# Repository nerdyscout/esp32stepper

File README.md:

# ESP32STEPPER

current state: untested :warning:

inspired by [joshr120/PD-Stepper](https://github.com/joshr120/PD-Stepper) but being fully open hardware/software.

Stepper motor controller using Trinamic TMC2208, ESP32-S3 and USB-PD mountable onto any NEMA17 motor. 

## Main Features:
- **ESP32-S3**
  - alternatively a LM555 pulse generator can be used.
- **USB Power Delivery** providing up to 20V operation
  - alternatively 9-24 Volt external supply 
- **TMC2208** silent stepper motor driver
- optional
  - rotary encoder:
    - **AS5048B** 14-Bit angular position sensor
    - **MPU-9250** 9-axis motion sensor
  - 0.96" 128x96 **LC-Display**
  - **BME280** temperature sensor
  - **QWIIC** connector for external I2C components
  - **JTAG** pins accessible
  - **3 GPIO** pins and **UART** available
  - 2x **WS2812** RGB LEDs
  - 2x **Push Buttons**

## PCB

### Schematic

### Bill of Materials

The complete BOM is available in different formats:
  - interactive [HTML](https://nerdyscout.github.io/esp32stepper/pcb/docs/bom/esp32stepper-ibom.html)
<!--  - [octopart](pcb/docs/bom/esp32stepper-octopart.csv) -->
  - [Excel](pcb/docs/bom/esp32stepper-bom.xlsx)

### Fabrication

#### Layout

<table border="0" width="100%">
  <tr>
    <th><strong>Top</strong></th>
    <th><strong>Bottom</strong></th>
  </tr>
  <tr>
    <td></td>
    <td></td>
  </tr>
</table>

All fabrication files needed to produce this PCB are located within the [release package](https://github.com/nerdyscout/esp32stepper/releases).

#### Assembly Variants

There are two options to power this board, do not connect both at the same time!
- via connector *PWR* an **external 9-24 Voltage** can be applied which than also will be used to power the stepper motor. 
- **USB-PD** by setting the CFG pins a voltage is selected. This can be made either by assembling the resistors or in firmware of the ESP32.

There are as well two options for controlling the board:
- The **LM555** gives some basic PWM frequency driving the stepper controller. Instead of the external rotary encoder a potentiometer can be connected and choosing R15, R16 and C18 correctly should allow any stepping frequency.
- using the **ESP32-S3** gives much more options as it allows to utilize the I2C components (LC Display, accelerometer, temperature sensor), two RGB Leds and dynamically sets USB voltage.

Microstepping can be enabled by setting jumper MS1 and MS2.

## Mechanics

in the folder `cad` the spacers between motor and PCB, as well as the top housing, can be found. The spacer below the stepper controller should be made out of metal so it could act as heat sink, the other part can be simply 3D printed. If the external power connector is not assembled those two spacer parts could be manufactured with less hight, this brings the hall sensor closer to the magnet which needs to be glued onto the motor axis. 

## Firmware

### ESPHome

There is a [esphome](https://esphome.io/) config file supporting various features located at `firmware/esphome`

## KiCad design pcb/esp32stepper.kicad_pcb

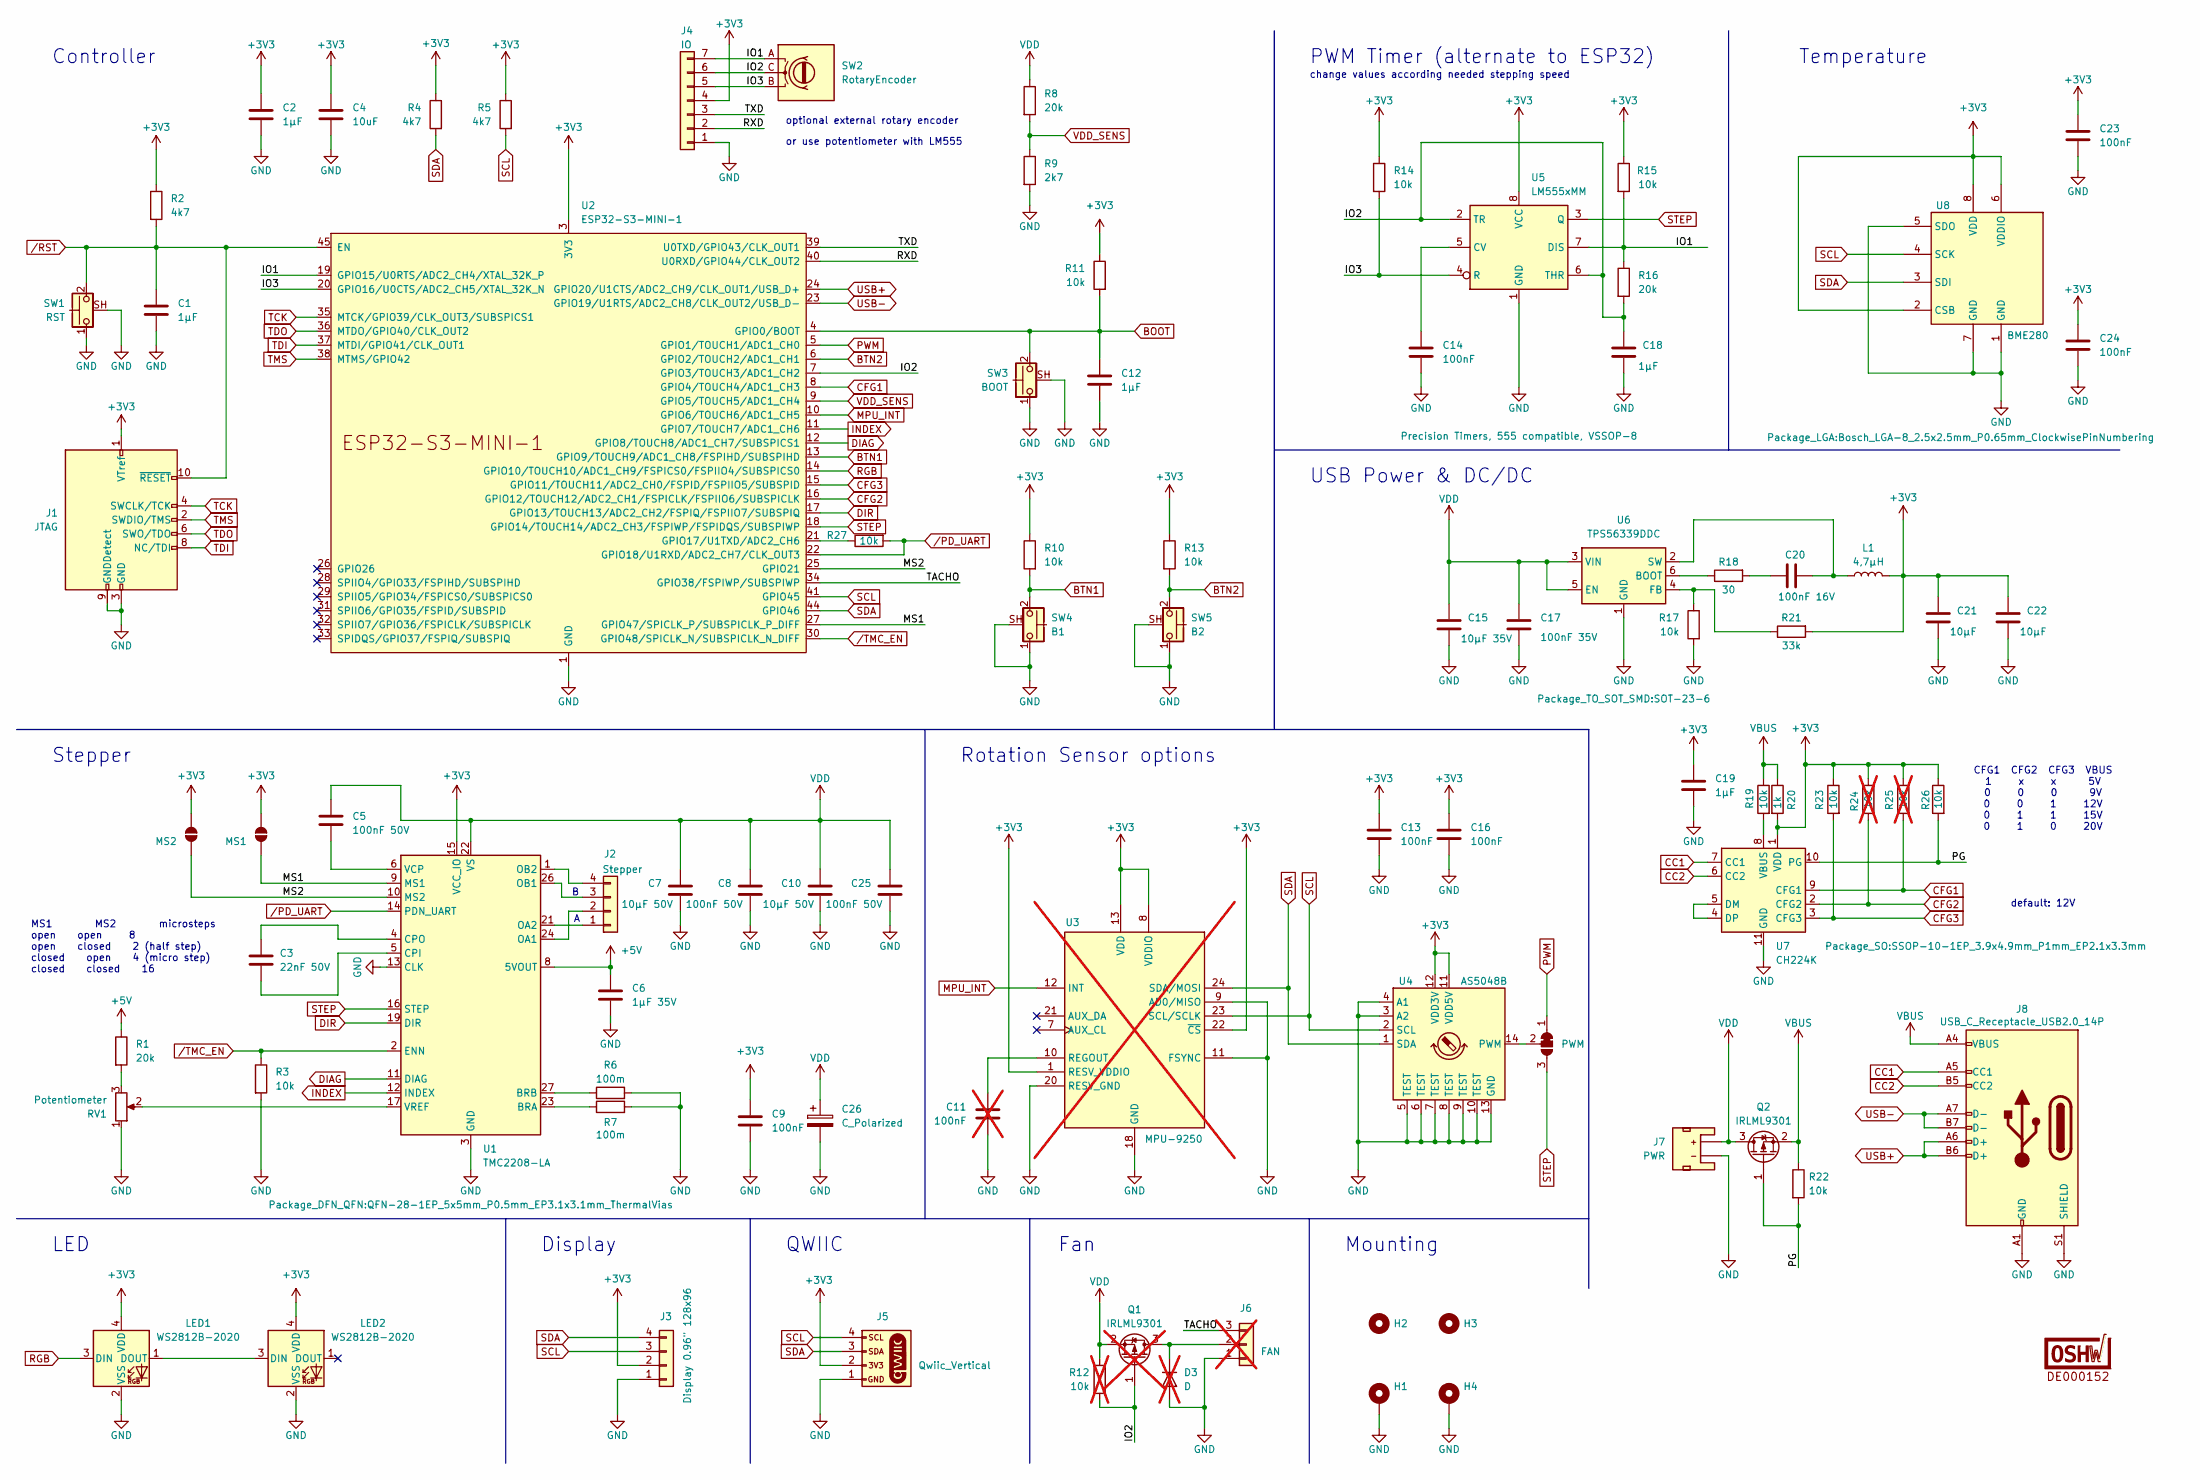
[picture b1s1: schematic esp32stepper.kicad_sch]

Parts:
C1, C2, C12, C19: 1µF; C_0402_1005Metric; LCSC C14445
C3: 22nF 50V; C_0402_1005Metric; LCSC C380305
C4: 10uF; C_0603_1608Metric; LCSC C22367827
C5, C8, C25: 100nF 50V; C_0603_1608Metric; LCSC C91183
C6: 1µF 35V; C_0603_1608Metric; LCSC C7432774
C7, C10: 10µF 50V; C_1206_3216Metric; LCSC C7432781
C9, C13, C16, C23, C24: 100nF; C_0402_1005Metric; LCSC C7432762
C11: 100nF; C_0402_1005Metric_Pad0.74x0.62mm_HandSolder; LCSC C7432762; not fitted
C14: 100nF; C_0402_1005Metric_Pad0.74x0.62mm_HandSolder; LCSC C7432762
C15: 10µF 35V; C_0603_1608Metric; LCSC C22367827
C17: 100nF 35V; C_0603_1608Metric; LCSC C5342943
C18: 1µF; C_0603_1608Metric_Pad1.08x0.95mm_HandSolder
C20: 100nF 16V; C_0402_1005Metric; LCSC C7432762
C21, C22: 10µF; C_0402_1005Metric; LCSC C5252392
C26: C_Polarized; CP_Elec_5x5.4; LCSC C22387982
D3: D; D_SOD-123; LCSC C95872; not fitted
H1, H2, H3, H4: MountingHole_Pad; MountingHole_3.2mm_M3_Pad_Via
J1: JTAG; PinHeader_2x05_P1.27mm_Vertical_SMD
J2: Stepper; JST_PH_S4B-PH-K_1x04_P2.00mm_Horizontal; LCSC C19271361
J3: Display 0.96" 128x96; PinSocket_1x04_P2.54mm_Vertical
J4: IO; JST_SH_SM07B-SRSS-TB_1x07-1MP_P1.00mm_Horizontal; LCSC C160406
J5: Qwiic_Vertical; JST_SH_SM04B-SRSS-TB_1x04-1MP_P1.00mm_Horizontal; LCSC C160404
J6: FAN; Harwin_M20-89003xx_1x03_P2.54mm_Horizontal; not fitted
J7: PWR; JST_SMD_2.0mm-2
J8: USB_C_Receptacle_USB2.0_14P; USB_C_Receptacle_G-Switch_GT-USB-7010ASV; LCSC C2988369
JP1: MS2; SolderJumper-2_P1.3mm_Open_RoundedPad1.0x1.5mm
JP2: MS1; SolderJumper-2_P1.3mm_Open_RoundedPad1.0x1.5mm
JP3: PWM; SolderJumper-3_P1.3mm_Bridged12_RoundedPad1.0x1.5mm
L1: 4,7µH; L_Bourns-SRN4018; LCSC C1330726
LED1, LED2: WS2812B-2020; LED_WS2812B-2020_PLCC4_2.0x2.0mm; LCSC C965555
LOGO1: OSHW-Certification-Mark-Stacked_8x7mm_SilkScreen
Q1: IRLML9301; SOT-23; LCSC C7472922; not fitted
Q2: IRLML9301; SOT-23; LCSC C7472922
R1, R8: 20k; R_0402_1005Metric; LCSC C93942
R2, R4, R5: 4k7; R_0402_1005Metric; LCSC C159885
R3, R10, R11, R13, R17, R19, R22, R23, R26, R27: 10k; R_0402_1005Metric; LCSC C854480
R6, R7: 100m; R_0805_2012Metric; LCSC C2935234
R9: 2k7; R_0402_1005Metric; LCSC C203149
R12, R24, R25: 10k; R_0402_1005Metric; LCSC C304153; not fitted
R14, R15: 10k; R_0402_1005Metric_Pad0.72x0.64mm_HandSolder; LCSC C304153
R16: 20k; R_0402_1005Metric_Pad0.72x0.64mm_HandSolder; LCSC C93942
R18: 30; R_0402_1005Metric; LCSC C965208
R20: 1k; R_0402_1005Metric; LCSC C11702
R21: 33k; R_0402_1005Metric; LCSC C138003
RV1: Potentiometer; Potentiometer_Bourns_TC33X_Vertical; LCSC C720648
SW1: RST; SW_SPST_CK_KMS2xxGP; LCSC C221699
SW2: RotaryEncoder
SW3: BOOT; SW_SPST_CK_KMS2xxGP; LCSC C221699
SW4: B1; SW_SPST_CK_KMS2xxGP; LCSC C221699
SW5: B2; SW_SPST_CK_KMS2xxGP; LCSC C221699
U1: TMC2208-LA; QFN-28-1EP_5x5mm_P0.5mm_EP3.1x3.1mm_ThermalVias; LCSC C115944
U2: ESP32-S3-MINI-1; LCSC C2913206
U3: MPU-9250; InvenSense_QFN-24_3x3mm_P0.4mm; LCSC C71459; not fitted
U4: AS5048B; TSSOP-14_4.4x5mm_P0.65mm; LCSC C2655184
U5: LM555xMM; VSSOP-8_3x3mm_P0.65mm
U6: TPS56339DDC; SOT-23-6; LCSC C2071106
U7: CH224K; SSOP-10-1EP_3.9x4.9mm_P1mm_EP2.1x3.3mm; LCSC C970725
U8: BME280; Bosch_LGA-8_2.5x2.5mm_P0.65mm_ClockwisePinNumbering; LCSC C92489

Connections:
+3V3: C2.1, C4.1, C9.1, C13.1, C16.1, C19.1, C21.1, C22.1, C23.1, C24.1, J1.1 (VTref), J3.2, J4.4, J5.2, JP1.1 (A), JP2.1 (A), L1.2, LED1.4 (VDD), LED2.4 (VDD), R2.1, R4.1, R5.1, R10.1, R11.1, R13.1, R14.1, R15.1, R20.2, R21.2, R23.1, R24.1, R25.1, R26.1, U1.15 (VCC_IO), U2.3 (3V3), U3.1 (RESV_VDDIO), U3.8 (VDDIO), U3.13 (VDD), U3.22 (~CS), U4.11 (VDD5V), U4.12 (VDD3V), U5.8 (VCC), U7.1 (VDD), U8.2 (CSB), U8.6 (VDDIO), U8.8 (VDD)
+5V: C6.1, R1.1, U1.8 (5VOUT)
/IO1: J4.7, R15.2, R16.1, SW2.A, U2.19 (GPIO15/U0RTS/ADC2_CH4/XTAL_32K_P), U5.7 (DIS)
/IO2: C18.1, J4.6, Q1.1 (G), R12.2, R16.2, SW2.C, U2.7 (GPIO3/TOUCH3/ADC1_CH2), U5.2 (TR), U5.6 (THR)
/IO3: J4.5, R14.2, SW2.B, U2.20 (GPIO16/U0CTS/ADC2_CH5/XTAL_32K_N), U5.4 (R)
/MS1: JP2.2 (B), U1.9 (MS1), U2.27 (GPIO47/SPICLK_P/SUBSPICLK_P_DIFF)
/MS2: JP1.2 (B), U1.10 (MS2), U2.25 (GPIO21)
/PG: Q2.1 (G), R22.2, R26.2, U7.10 (PG)
/RXD: J4.2, U2.40 (U0RXD/GPIO44/CLK_OUT2)
/TACHO: J6.3, U2.34 (GPIO38/FSPIWP/SUBSPIWP)
/TXD: J4.3, U2.39 (U0TXD/GPIO43/CLK_OUT1)
BOOT: C12.1, R11.2, SW3.2, U2.4 (GPIO0/BOOT)
BTN1: R10.2, SW4.2, U2.13 (GPIO9/TOUCH9/ADC1_CH8/FSPIHD/SUBSPIHD)
BTN2: R13.2, SW5.2, U2.6 (GPIO2/TOUCH2/ADC1_CH1)
CC1: J8.A5 (CC1), U7.7 (CC1)
CC2: J8.B5 (CC2), U7.6 (CC2)
CFG1: R25.2, U2.8 (GPIO4/TOUCH4/ADC1_CH3), U7.9 (CFG1)
CFG2: R24.2, U2.16 (GPIO12/TOUCH12/ADC2_CH1/FSPICLK/FSPIIO6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), U7.2 (CFG2)
CFG3: R23.2, U2.15 (GPIO11/TOUCH11/ADC2_CH0/FSPID/FSPIIO5/S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), U7.3 (CFG3)
DIAG: U1.11 (DIAG), U2.12 (GPIO8/TOUCH8/ADC1_CH7/SUBSPICS1)
DIR: U1.19 (DIR), U2.17 (GPIO13/TOUCH13/ADC2_CH2/FSPIQ/FSPIIO7/S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)
GND: C1.2, C2.2, C4.2, C6.2, C7.2, C8.2, C9.2, C10.2, C11.2, C12.2, C13.2, C14.2, C15.2, C16.2, C17.2, C18.2, C19.2, C21.2, C22.2, C23.2, C24.2, C25.2, C26.2, D3.2 (A), H1.1, H4.1, J1.3 (GND), J1.5 (GND), J1.9 (GNDDetect), J3.1, J4.1, J5.1, J6.1, J7.1 (-), J8.A1 (GND), J8.A12 (GND), J8.B1 (GND), J8.B12 (GND), J8.S1 (SHIELD), LED1.2 (VSS), LED2.2 (VSS), R3.2, R6.2, R7.2, R9.2, R17.2, RV1.1, SW1.1, SW1.SH (B), SW3.1, SW3.SH (B), SW4.1, SW4.SH (B), SW5.1, SW5.SH (B), U1.3 (GND), U1.13 (CLK), U1.18 (GND), U1.29 (GND), U2.1 (GND), U2.2 (GND), U2.42 (GND), U2.43 (GND), U2.46 (GND), U2.47 (GND), U2.48 (GND), U2.49 (GND), U2.50 (GND), U2.51 (GND), U2.52 (GND), U2.53 (GND), U2.54 (GND), U2.55 (GND), U2.56 (GND), U2.57 (GND), U2.58 (GND), U2.59 (GND), U2.60 (GND), U2.61 (GND), U2.62 (GND), U2.63 (GND), U2.64 (GND), U2.65 (GND), U3.9 (AD0/MISO), U3.11 (FSYNC), U3.18 (GND), U3.20 (RESV_GND), U4.3 (A2), U4.4 (A1), U4.5 (TEST), U4.6 (TEST), U4.7 (TEST), U4.8 (TEST), U4.9 (TEST), U4.10 (TEST), U4.13 (GND), U5.1 (GND), U6.1 (GND), U7.11 (GND), U8.1 (GND), U8.5 (SDO), U8.7 (GND)
INDEX: U1.12 (INDEX), U2.11 (GPIO7/TOUCH7/ADC1_CH6)
MPU_INT: U2.10 (GPIO6/TOUCH6/ADC1_CH5), U3.12 (INT)
unnamed: C20.1, R18.2
unnamed: D3.1 (K), J6.2, Q1.3 (D)
unnamed: J2.1, U1.21 (OA2)
unnamed: J2.2, U1.24 (OA1)
unnamed: J2.3, U1.26 (OB1)
unnamed: J2.4, U1.1 (OB2)
unnamed: JP3.2 (C), U4.14 (PWM)
unnamed: LED1.1 (DOUT), LED2.3 (DIN)
unnamed: R1.2, RV1.3
unnamed: R7.1, U1.23 (BRA)
unnamed: R6.1, U1.27 (BRB)
unnamed: C3.2, U1.5 (CPI)
unnamed: C3.1, U1.4 (CPO)
unnamed: C5.2, U1.6 (VCP)
unnamed: RV1.2, U1.17 (VREF)
unnamed: R27.1, U2.21 (GPIO17/U1TXD/ADC2_CH6)
unnamed: C11.1, U3.10 (REGOUT)
unnamed: C14.1, U5.5 (CV)
unnamed: R18.1, U6.6 (BOOT)
unnamed: R17.1, R21.1, U6.4 (FB)
unnamed: C20.2, L1.1, U6.2 (SW)
unnamed: U7.4 (DP), U7.5 (DM)
unnamed: R19.2, U7.8 (VBUS)
PWM: JP3.1 (A), U2.5 (GPIO1/TOUCH1/ADC1_CH0)
RGB: LED1.3 (DIN), U2.14 (GPIO10/TOUCH10/ADC1_CH9/FSPICS0/FSPIIO4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)
SCL: J3.3, J5.4, R5.2, U2.41 (GPIO45), U3.23 (SCL/SCLK), U4.2 (SCL), U8.4 (SCK)
SDA: J3.4, J5.3, R4.2, U2.44 (GPIO46), U3.24 (SDA/MOSI), U4.1 (SDA), U8.3 (SDI)
STEP: JP3.3 (B), U1.16 (STEP), U2.18 (GPIO14/TOUCH14/ADC2_CH3/FSPIWP/FSPIDQS/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), U5.3 (Q)
TCK: J1.4 (SWCLK/TCK), U2.35 (MTCK/GPIO39/CLK_OUT3/SUBSPICS1)
TDI: J1.8 (NC/TDI), U2.37 (MTDI/GPIO41/CLK_OUT1)
TDO: J1.6 (SWO/TDO), U2.36 (MTDO/GPIO40/CLK_OUT2)
TMS: J1.2 (SWDIO/TMS), U2.38 (MTMS/GPIO42)
USB+: J8.A6 (D+), J8.B6 (D+), U2.24 (GPIO20/U1CTS/ADC2_CH9/CLK_OUT1/USB_D+)
USB-: J8.A7 (D-), J8.B7 (D-), U2.23 (GPIO19/U1RTS/ADC2_CH8/CLK_OUT2/USB_D-)
VBUS: J8.A4 (VBUS), J8.A9 (VBUS), J8.B4 (VBUS), J8.B9 (VBUS), Q2.2 (S), R19.1, R20.1, R22.1
VDD: C5.1, C7.1, C8.1, C10.1, C15.1, C17.1, C25.1, C26.1, J7.2 (+), Q1.2 (S), Q2.3 (D), R8.1, R12.1, U1.22 (VS), U1.28 (VS), U6.3 (VIN), U6.5 (EN)
VDD_SENS: R8.2, R9.1, U2.9 (GPIO5/TOUCH5/ADC1_CH4)
/PD_UART: R27.2, U1.14 (PDN_UART), U2.22 (GPIO18/U1RXD/ADC2_CH7/CLK_OUT3)
/RST: C1.1, J1.10 (~RESET), R2.2, SW1.2, U2.45 (EN)
/TMC_EN: R3.1, U1.2 (ENN), U2.30 (GPIO48/SPICLK_N/SUBSPICLK_N_DIFF)

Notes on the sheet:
Mounting
LED
Rotation Sensor options
Display
default: 12V
Temperature
CFG1 CFG2 CFG3 VBUS 1 x x 5V 0 0 0 9V 0 0 1 12V 0 1 1 15V 0 1 0 20V
optional external rotary encoder
Stepper
USB Power & DC/DC
QWIIC
Controller
MS1 MS2 microsteps open open 8 open closed 2 (half step) closed open 4 (micro step) closed closed 16
Fan
PWM Timer (alternate to ESP32)
change values according needed stepping speed
or use potentiometer with LM555

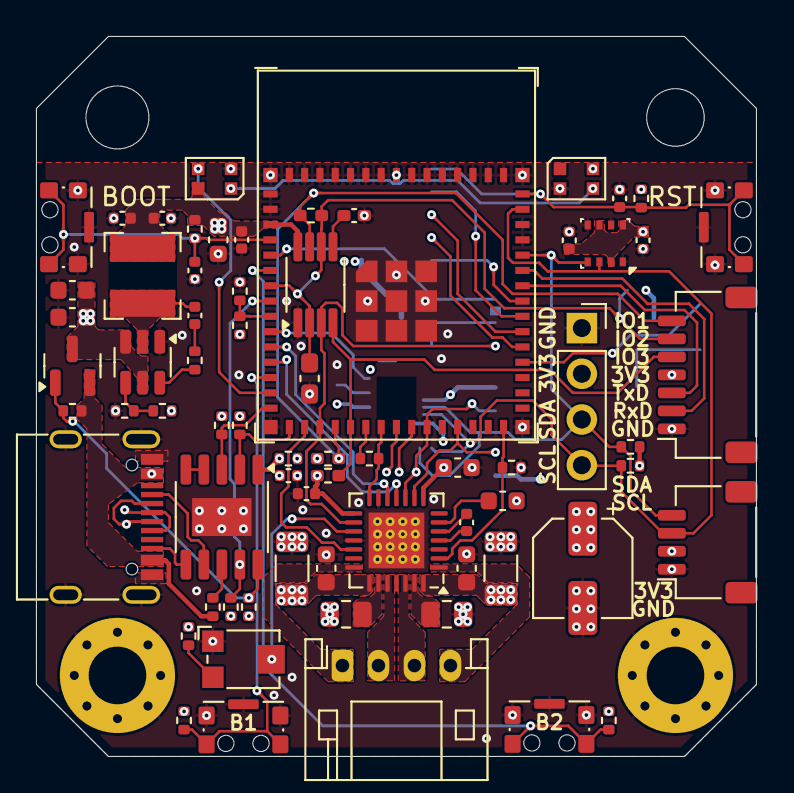
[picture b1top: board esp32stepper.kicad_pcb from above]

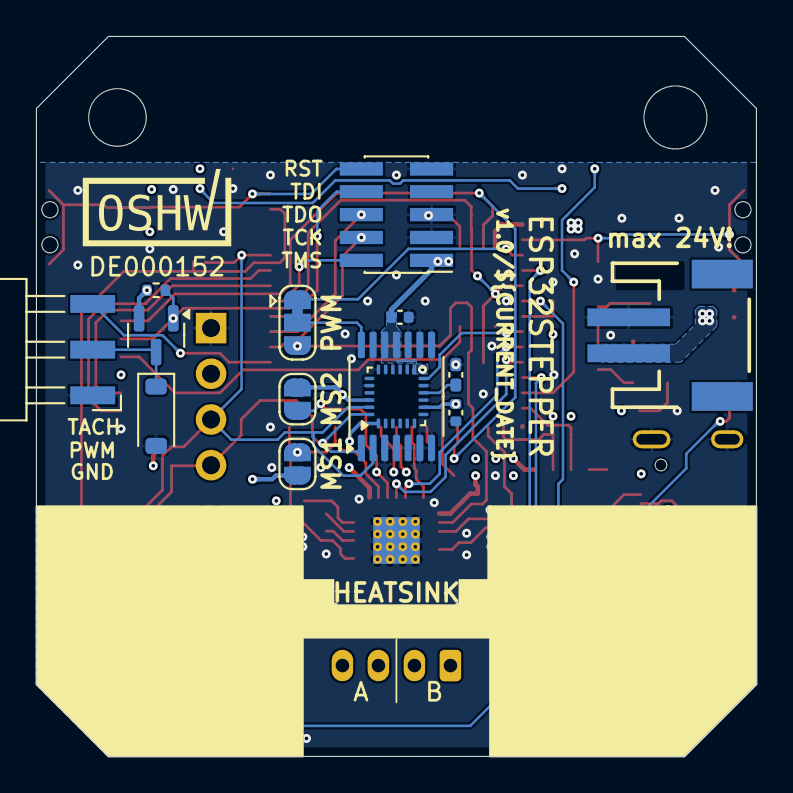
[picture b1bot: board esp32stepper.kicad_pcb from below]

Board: 4 copper layers, 40.0 x 40.0 mm, 88 parts (15 on the bottom side), 64 nets.

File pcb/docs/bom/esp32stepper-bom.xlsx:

Component | Description | Part | References | Value | Footprint | Quantity Per PCB | Datasheet | lcsc | variant | sim.device | sim.pins | prod_id
1 | Unpolarized capacitor | C | C9C13C16C23C24 | 100nF | C_0402_1005Metric | 5 | ~ | C7432762
2 | Unpolarized capacitor | C | C1C2C12C19 | 1µF | C_0402_1005Metric | 4 | ~ | C14445 | ESP32 USBPD
3 | Unpolarized capacitor | C | C21C22 | 10µF | C_0402_1005Metric | 2 | ~ | C5252392
4 | Unpolarized capacitor | C | C4 | 10uF | C_0603_1608Metric | 1 | ~ | C22367827
5 | Unpolarized capacitor | C | C20 | 100nF 16V | C_0402_1005Metric | 1 | ~ | C7432762
6 | Unpolarized capacitor | C | C17 | 100nF 35V | C_0603_1608Metric | 1 | ~ | C5342943
7 | Unpolarized capacitor | C | C5C8C25 | 100nF 50V | C_0603_1608Metric | 3 | ~
8 | Unpolarized capacitor | C | C15 | 10µF 35V | C_0603_1608Metric | 1 | ~ | C22367827
9 | Unpolarized capacitor | C | C7C10 | 10µF 50V | C_1206_3216Metric | 2 | ~
10 | Unpolarized capacitor | C | C6 | 1µF 35V | C_0603_1608Metric | 1 | ~ | C7432774
11 | Unpolarized capacitor | C | C3 | 22nF 50V | C_0402_1005Metric | 1 | ~
12 | Generic connector, single row, 01x07, script generated (kicad-library-utils/sch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 | Conn_01x07 | J4 | IO | JST_SH_SM07B-SRSS-TB_1x07-1MP_P1.00mm_Horizontal | 1 | https://www.jst-mfg.com/product/pdf/eng/eSH.pdf | C160406
13 | 4 pin JST 1mm polarized connector for I2C | Qwiic_Vertical | J5 | Qwiic_Vertical | JST_SH_SM04B-SRSS-TB_1x04-1MP_P1.00mm_Horizontal | 1 | https://www.jst-mfg.com/product/pdf/eng/eSH.pdf | C160404 |  |  |  | CONN-14483
14 | Generic connector, single row, 01x04, script generated (kicad-library-utils/sch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 | Conn_01x04 | J2 | Stepper | JST_PH_S4B-PH-K_1x04_P2.00mm_Horizontal | 1 | ~ | C19271361
15 | USB 2.0-only 14P Type-C Receptacle connector | USB_C_Receptacle_USB2.0_14P | J8 | USB_C_Receptacle_USB2.0_14P | USB_C_Receptacle_G-Switch_GT-USB-7010ASV | 1 | https://www.usb.org/sites/default/files/documents/usb_type-c.zip | C2988369 | USBPD
16 | Inductor | L | L1 | 4,7µH | L_Bourns-SRN4018 | 1 | ~ | C1330726
17 | RGB LED with integrated controller, 2.0 x 2.0 mm, 12 mA | WS2812B-2020 | LED1LED2 | WS2812B-2020 | LED_WS2812B-2020_PLCC4_2.0x2.0mm | 2 | https://cdn-shop.adafruit.com/product-files/4684/4684_WS2812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 | C965555 | ESP32
18 | -3.6A Id, -30V Vds, 64mOhm Rds, P-Channel HEXFET Power MOSFET, SOT-23 | IRLML9301 | Q2 | IRLML9301 | SOT-23 | 1 | https://www.infineon.com/dgdl/irlml9301pbf.pdf?fileId=5546d4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 | C7472922
19 | Resistor | R | R6R7 | 100m | R_0805_2012Metric | 2 | ~ | C2935234
20 | Resistor | R | R18 | 30 | R_0402_1005Metric | 1 | ~ | C965208
21 | Resistor | R | R20 | 1k | R_0402_1005Metric | 1 | ~ | C2077651 | USBPD
22 | Resistor | R | R9 | 2k7 | R_0402_1005Metric | 1 | ~ | C203149 | ESP32
23 | Resistor | R | R2R4R5 | 4k7 | R_0402_1005Metric | 3 | ~ | C159885 | ESP32
24 | Resistor | R | R3R10R11R13R17R19R22R23R26R27 | 10k | R_0402_1005Metric | 10 | ~ | C2654005 | ESP32 USBPD
25 | Resistor | R | R1R8 | 20k | R_0402_1005Metric | 2 | ~ | C93942 | ESP32
26 | Resistor | R | R21 | 33k | R_0402_1005Metric | 1 | ~ | C427218
27 | Potentiometer | R_Potentiometer | RV1 | Potentiometer | Potentiometer_Bourns_TC33X_Vertical | 1 | ~ | C720648
28 | Microminiature SMT Side Actuated, 4.2 x 2.8 x 1.42mm, without pegs, with shield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 | CK_KMS2xxG | SW4 | B1 | SW_SPST_CK_KMS2xxGP | 1 | https://www.ckswitches.com/media/1482/kms.pdf | C221699 | ESP32
29 | Microminiature SMT Side Actuated, 4.2 x 2.8 x 1.42mm, without pegs, with shield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 | CK_KMS2xxG | SW5 | B2 | SW_SPST_CK_KMS2xxGP | 1 | https://www.ckswitches.com/media/1482/kms.pdf | C221699 | ESP32
30 | Microminiature SMT Side Actuated, 4.2 x 2.8 x 1.42mm, without pegs, with shield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 | CK_KMS2xxG | SW3 | BOOT | SW_SPST_CK_KMS2xxGP | 1 | https://www.ckswitches.com/media/1482/kms.pdf | C221699 | ESP32
31 | Microminiature SMT Side Actuated, 4.2 x 2.8 x 1.42mm, without pegs, with shield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 | CK_KMS2xxG | SW1 | RST | SW_SPST_CK_KMS2xxGP | 1 | https://www.ckswitches.com/media/1482/kms.pdf | C221699 | ESP32
32 | Magnetic position sensor, 14-bit, PWM output, I2C Interface, TSSOP-14 | AS5048B | U4 | AS5048B | TSSOP-14_4.4x5mm_P0.65mm | 1 | https://ams.com/documents/20143/36005/AS5048_DS000298_4-00.pdf
33 | 3-in-1 sensor, humidity, pressure, temperature, I2C and SPI interface, 1.71-3.6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 | BME280 | U8 | BME280 | Bosch_LGA-8_2.5x2.5mm_P0.65mm_ClockwisePinNumbering | 1 | https://www.bosch-sensortec.com/media/boschsensortec/downloa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 | C92489 | ESP32
34 | 100W USB Type-C PD3.0/2.0, BC1.2 Sink Controller, SSOP-10 | CH224K | U7 | CH224K | SSOP-10-1EP_3.9x4.9mm_P1mm_EP2.1x3.3mm | 1 | https://www.wch.cn/downloads/file/301.html | C970725 | USB
35 | Smallsized module supporting 2.4 GHz WiFi (802.11 b/g/n) and Bluetooth ® 5 (LE)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 | ESP32-S3-MINI-1 | U2 | ESP32-S3-MINI-1 | ESP32-S3-MINI-1 | 1 | https://www.espressif.com/sites/default/files/documentation/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 | C2913206 | ESP32
36 | Standalone driver for two-phase bipolar stepper motor, 2A, 4.75… 36V, UART, int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 | TMC2208-LA | U1 | TMC2208-LA | QFN-28-1EP_5x5mm_P0.5mm_EP3.1x3.1mm_ThermalVias | 1 | https://www.analog.com/media/en/technical-documentation/data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 | C115944
37 | 4.5V to 24V Input, 3-A Output Synchronous Buck Converter, SOT-23-6 | TPS56339DDC | U6 | TPS56339DDC | SOT-23-6 | 1 | https://www.ti.com/lit/ds/symlink/tps56339.pdf | C2071106
Component Groups: | 53
Component Count: | 82
Fitted Components: | 62
Number of PCBs: | 1
Total components: | 62
Schematic Version: | 1.1
Schematic Date: | 2025-05-02
BoM Date: | 2025-05-02T11:01:40+0000
Schematic Source: | esp32stepper.kicad_sch
KiCad Version: | Eeschema 9.0.1

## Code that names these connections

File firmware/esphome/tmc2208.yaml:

external_components:
  - source: github://slimcdk/esphome-custom-components
    components: [tmc2208_hub, tmc2208, stepper]
#  - source:
#      type: local
#      path: components

esphome:
  name: esp32stepper
  project:
    name: nerdyscout.esp32stepper
    version: "1.1"
  platformio_options:
    board_build.flash_mode: dio
    upload_speed: 921600
  on_boot:
    - tmc2208.configure:
        microsteps: 4
        direction: clockwise
        interpolation: true
    - tmc2208.currents:
        irun: 16
        ihold: 0
        tpowerdown: 0
        iholddelay: 0
        standstill_mode: freewheeling

    - output.turn_off: #Microstep resolution configuration (internal pull-down resistors: MS2, MS1: 00: 1/8, 01: 1/32, 10: 1/64 11: 1/16
        id: MS1_pin
    - output.turn_off:
        id: MS2_pin

      #set PD voltage  # 5V  9V  12V  15V  20V
    - output.turn_off: # 1   0    0    0    0
        id: CFG1_pin
    - output.turn_on: # -   0    0    1    1
        id: CFG2_pin
    - output.turn_off: # -   0    1    1    0
        id: CFG3_pin

esp32:
  board: esp32-s3-devkitc-1
  #  variant: esp32s3
  framework:
    type: arduino

  # This should point to the public location of this yaml file.
dashboard_import:
  package_import_url: github://nerdyscout/esp32stepper/firmware/esphome/tmc22208.yaml#main
  import_full_config: false # or true

ota:
  platform: esphome
  password: !secret ota_password

wifi:
  ssid: !secret wifi_ssid
  password: !secret wifi_password

web_server:
  version: 3
  port: 80

captive_portal:

mqtt:
  broker: !secret mqtt_broker
  username: !secret mqtt_username
  password: !secret mqtt_password

api:
  password: !secret api_password

logger:
#  level: DEBUG

i2c:
  sda: GPIO46
  scl: GPIO45
  scan: true
#  id: bus_a

uart:
  - id: serial_extern
    tx_pin: GPIO43
    rx_pin: GPIO44
    baud_rate: 115200
  - id: serial_stepper
    tx_pin: GPIO17
    rx_pin: GPIO18
    baud_rate: 115200

tmc2208_hub:
  id: tmc_hub
  uart_id: serial_stepper

output:
  - platform: gpio
    pin: GPIO21
    id: MS1_pin
  - platform: gpio
    pin: GPIO13
    id: MS2_pin

  - platform: gpio
    pin: GPIO14
    id: CFG1_pin
  - platform: gpio
    pin: GPIO12
    id: CFG2_pin
  - platform: gpio
    pin: GPIO11
    id: CFG3_pin

light:
  - platform: neopixelbus
    type: GRB
    variant: WS2812
    pin: GPIO10
    num_leds: 2
    id: led_rgb
  - platform: partition
    name: "RGB LED 1"
    segments:
      - id: led_rgb
        from: 0
        to: 0
  - platform: partition
    name: "RGB LED 2"
    segments:
      - id: led_rgb
        from: 1
        to: 1

stepper:
  - platform: tmc2208
    id: driver
    tmc2208_hub_id: tmc_hub
    max_speed: 800 steps/s
    acceleration: 1500 steps/s^2
    deceleration: 1500 steps/s^2
    rsense: 100 mOhm
    vsense: False
    enn_pin: GPIO09 # Enable not input pin for the driver.
    diag_pin: GPIO08 # Error signaling from the driver.
    index_pin: GPIO07 # Serves as stepping feedback from the internal step pulse generator
    step_pin: GPIO02 # Provides stepping pulses to the driver.
    dir_pin: GPIO04 # Controls direction of the motor.
    on_status:
      - logger.log:
          format: "Driver is reporting an update! (code %d)"
          args: ["code"]
# only supported by TMC2209
#    on_stall:
#      - logger.log: "Motor stalled!"
#      - stepper.stop: driver
#      - light.turn_on:
#          id: led_rgb
#          transition_length: 0s
#      - delay: 250ms
#      - light.turn_off:
#          id: led_rgb
#          transition_length: 1s

button:
  - platform: restart
    name: Restart

  - platform: template
    name: Stop
    on_press:
      - stepper.stop: driver

binary_sensor:
  - platform: gpio
    name: Button 1
    pin:
      number: GPIO47
      mode: INPUT
      inverted: true
    id: btn1
    filters:
      - delayed_on: 10ms

  - platform: gpio
    name: Button 2
    id: btn2
    pin:
      number: GPIO48
      mode: INPUT
      inverted: true
    filters:
      - delayed_on: 10ms

display:
  - platform: ssd1306_i2c
    model: "SSD1306 128x64"
    lambda: |-
      it.print(0, 0, id(roboto), "Hello World!");

sensor:
  #  - platform: bme280_i2c
  #    update_interval: 10s
  #    temperature:
  #      name: "BME280 Temperature"
  #    pressure:
  #      name: "BME280 Pressure"
  #    humidity:
  #      name: "BME280 Humidity"

  - platform: adc
    name: "VBUS Voltage"
    pin: GPIO05
    update_interval: 2s
    attenuation: 12dB
    filters:
      - multiply: 8.47742

  - platform: rotary_encoder
    name: "Rotary Encoder"
    pin_a: GPIO15
    pin_b: GPIO16
    pin_reset: GPIO03
    id: rotary
#    on_value:
#      then:
#        - stepper.set_target:
#            id: driver
#            target: !lambda "return id(rotary)->current_position;"

number:
  - platform: template
    name: Target position
    min_value: -10000
    max_value: 10000
    step: 10
    lambda: return id(driver)->current_position;
    update_interval: 1s
    set_action:
      - stepper.set_target:
          id: driver
          target: !lambda "return x;"

font:
  - file: "gfonts://Roboto"
    id: roboto
    size: 10

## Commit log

2025-03-27 init project
2025-03-27 Apply automatic changes
2025-03-27 ci: moved config files
2025-03-27 docs: add docs
2025-04-03 add license
2025-04-12 docs: add pdf output with RefDef, stackup and characteristics
2025-04-12 add OSHW id
2025-05-02 major update to v1.1
2025-06-21 add devcontainer with act and kibot
2025-06-21 refactor: move act installation to post-create script and update release workflow paths
2025-06-21 update pcb
2025-06-21 mend
2025-06-21 add permission

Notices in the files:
pcb/esp32stepper.kicad_pcb:
License: https://ohwr.org/cern_ohl_w_v2.txt (CERN-OHL-W)
